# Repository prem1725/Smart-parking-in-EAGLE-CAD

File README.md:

# Smart-parking-in-EAGLE-CAD
World's population is growing in a rapid sense. Because of this the parking becomes really tough in many cities and result in vehicles circulating in the streets. Smart parking systems have become a very helpful but they are usually complex and expensive. Their installation has to be done by specialized staff and even the structure needs to be modified. A lot of money and time should be spent on the maintenance. This system helps building a more simple and practical solution and also it is cheap. 

In this project that is build in EAGLE CAD we have a magnetic sensor and an IR sensor for evaluation purposes. The magnetic sensor would help the device to recognize any empty parking spot. The reason why I didn't use IR or UV sensor for this task is because UV sensor detects small objects like stones or the parking meter as an object and wouldn't be accurate.
IR sensor would detect the path for the parking however, it would detect the car with the same accuracy as magnetic sensor, hence IR sensor is used as an end sensor for perfect parking.

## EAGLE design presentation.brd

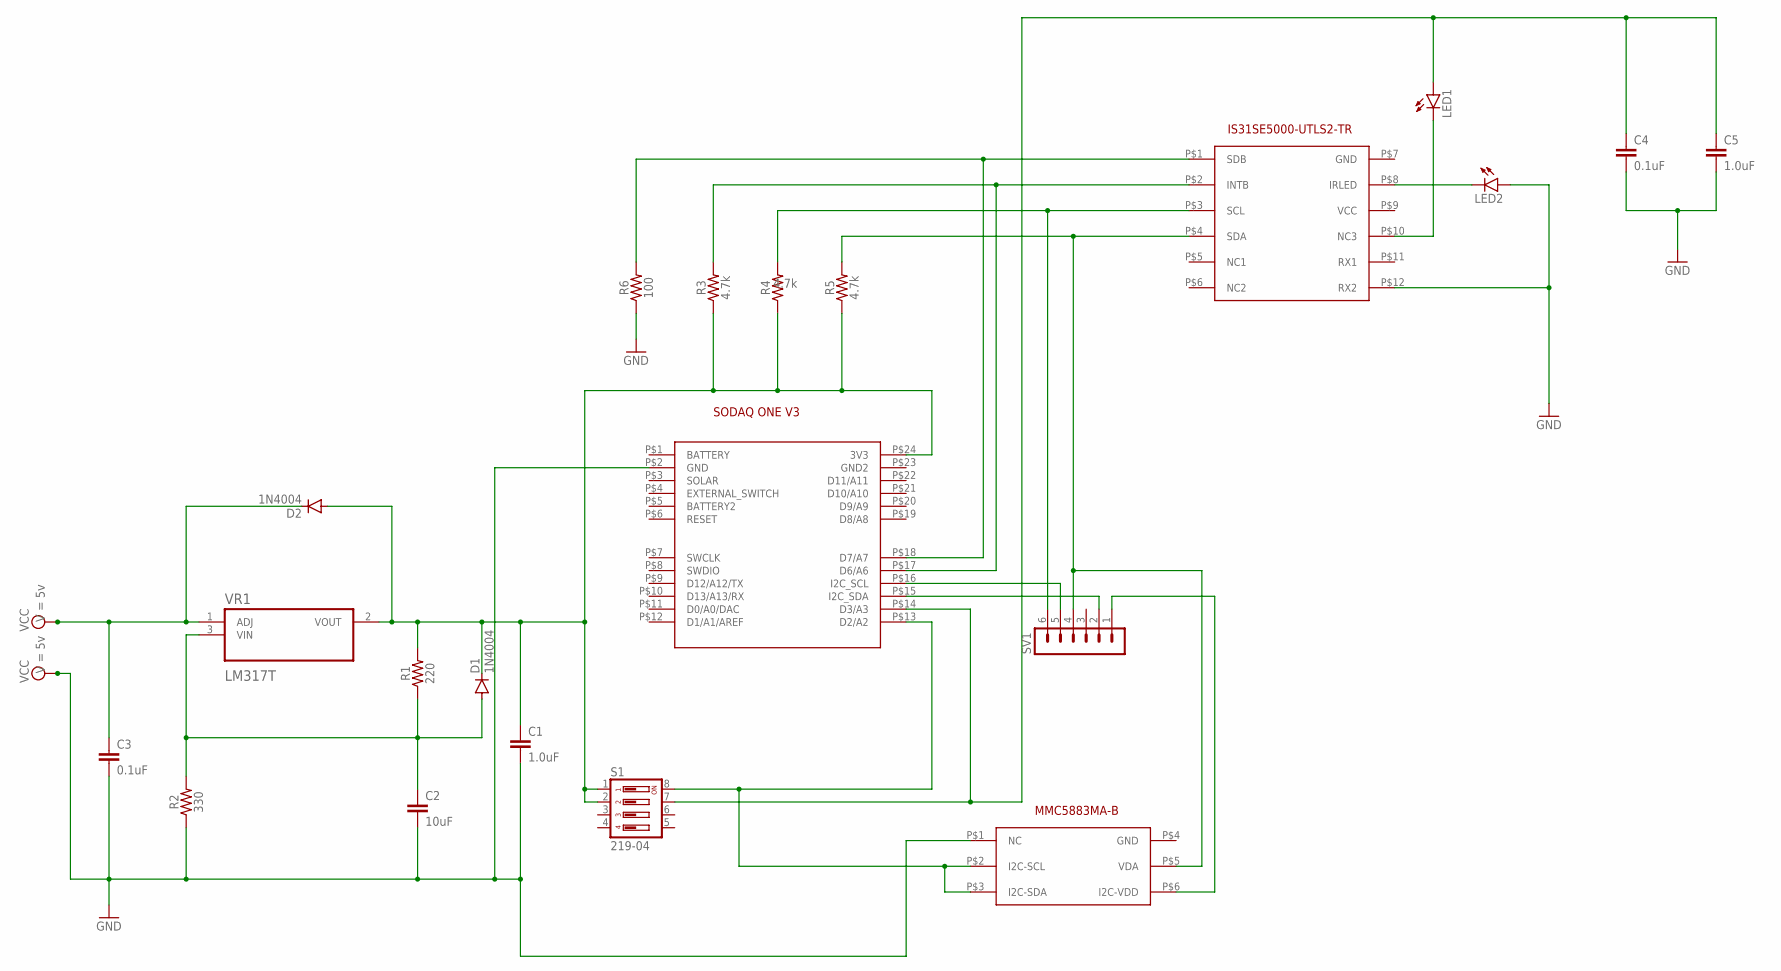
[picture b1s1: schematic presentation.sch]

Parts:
C1, C5: 1.0uF; 0402
C2: 10uF; 0603
C3, C4: 0.1uF; 0402
D1, D2: 1N4004; DO41-10
LED1, LED2: LED5MM
R1: 220; 0603
R2: 330; 0603
R3, R4, R5: 4.7k; 0603
R6: 100; 0603
S1: 219-04; CTS-219-04
SV1: MA06-1
U$1: SODAQONE
U$2: MMC5883MA-B
U$3: IS31SE5000
VR1: LM317T; TO254P1054X470X1955-3

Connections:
GND: C4.2, C5.2, LED2.A, R6.1, U$3.P$12 (RX2)
unnamed: C1.1, D1.C, D2.A, R1.2, R3.1, R4.1, R5.1, S1.1, S1.2, U$1.P$24 (3V3), VR1.2 (VOUT)
unnamed: SV1.1, U$2.P$6 (I2C-VDD)
unnamed: R5.2, SV1.4, U$2.P$5 (VDA), U$3.P$4 (SDA)
unnamed: S1.8, U$1.P$13 (D2/A2), U$2.P$2 (I2C-SCL), U$2.P$3 (I2C-SDA)
unnamed: C4.1, C5.1, LED1.A, S1.7, U$1.P$14 (D3/A3)
unnamed: C2.1, D1.A, R1.1, R2.2, VR1.3 (VIN)
unnamed: R6.2, U$1.P$18 (D7/A7), U$3.P$1 (SDB)
unnamed: R3.2, U$1.P$17 (D6/A6), U$3.P$2 (INTB)
unnamed: R4.2, SV1.6, U$3.P$3 (SCL)
unnamed: LED2.K (C), U$3.P$8 (IRLED)
unnamed: LED1.K (C), U$3.P$10 (NC3)
unnamed: SV1.2, U$1.P$15 (I2C_SDA)
unnamed: SV1.5, U$1.P$16 (I2C_SCL)
VCC: C1.2, C2.2, C3.1, C3.2, D2.C, R2.1, U$1.P$2 (GND), U$2.P$1 (NC), VR1.1 (ADJ)

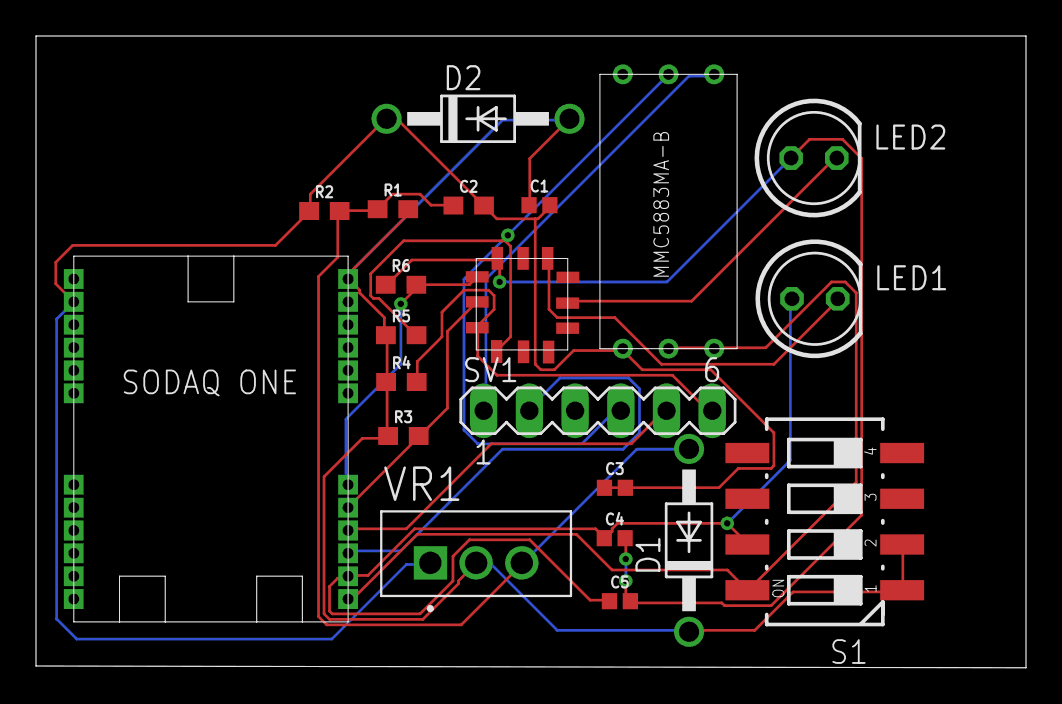
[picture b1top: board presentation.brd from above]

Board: 2 copper layers, 55.0 x 35.1 mm, 21 parts (0 on the bottom side), 15 nets.

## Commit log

2021-03-30 Add files via upload
    Schematic for the PCB
2021-03-30 Add files via upload
    board layout
2021-03-30 Add files via upload
    Magnetic sensor library
    IR sensor Library
    SODAQONE library

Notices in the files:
parts and their libraries:
SparkFun-Capacitors: Licensing: Creative Commons ShareAlike 4.0 International - https://creativecommons.org/licenses/by-sa/4.0
